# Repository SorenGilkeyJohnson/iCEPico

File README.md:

# iCEPico

> A compact development board combining the **RP2350** microcontroller and the **ICE40UP5K-SG48I** FPGA in a Raspberry Pi Pico form factor.

---

## Overview

The iCEPico is a custom PCB that pairs the RP2350 with the Lattice ICE40UP5K-SG48I FPGA. The board is modelled after the Raspberry Pi Pico, with the addition of the FPGA and a +1V2 regulator to supply it. The board matches the physical dimensions of the Pico, though it does **not** replicate the Pico's pinout.

I made this project because I wanted to learn FPGA design. Initially, I thought about using a BGA package but decided to go with QFN instead due to PCB costs and complexity. I had previously designed for the RP2040 but never the RP2350. I plan to use the project as a general-purpose dev board, a learning tool for FPGAs for me, and to teach students at my school's robotics club.

---
[Here is KiCanvas!](https://kicanvas.org/?repo=https%3A%2F%2Fgithub.com%2FSorenGilkeyJohnson%2FiCEPico%2Ftree%2Fmain%2FKiCad)

## Board Images

<table>
  <tr>
    <td align="center"><strong>Top View</strong></td>
    <td align="center"><strong>Bottom View</strong></td>
  </tr>
  <tr>
    <td></td>
    <td></td>
  </tr>
  <tr>
    <td align="center"><strong>3D Top</strong></td>
    <td align="center"><strong>3D Bottom</strong></td>
  </tr>
  <tr>
    <td></td>
    <td></td>
  </tr>
</table>

 [View Schematic (PDF)](Images/ICE40UP5K-SG48I_Schematic.pdf)

---

## Hardware

| Component | Part |
|-----------|------|
| Microcontroller | RP2350 |
| FPGA | Lattice ICE40UP5K-SG48I |
| QSPI Flash | W25Q128JVP |
| 3.3V Regulator | AP63203 (Buck) |
| 1.2V Regulator | TLV75612PDBV (LDO) |

### RP2350 <-> FPGA Interconnect

The FPGA flash is the RP2350 via bit-banging. The two chips share **8 GPIO lines** aligned to the RP2350's HSTX peripheral.

### PCB Stack-Up

| Layer | Function |
|-------|----------|
| 1 | Signal / Components |
| 2 | GND |
| 3 | PWR (primarily 3V3) |
| 4 | Signal |

---

## Power

The board can be powered via:
- **USB-C**      : 5V VBUS through a Schottky diode
- **VIN header** : direct voltage input

---

## Programming

| Method | Target | Description |
|--------|--------|-------------|
| USB (UF2) | RP2350 | Drag-and-drop bootloader over USB-C |
| SWD | RP2350 | Debug header for OpenOCD / probe-rs |
| Bit-bang (via RP2350) | ICE40 FPGA | FPGA bitstream loaded by the RP2350 firmware |

---

## Pinout

| Pin | Left Signal | | Right Signal | Pin |
|-----|------------|---|-------------|-----|
| 1  | GND        | | +3V3        | 2  |
| 3  | GPIO0      | | +VIN        | 4  |
| 5  | GPIO1      | | ADC2        | 6  |
| 7  | GPIO2      | | ADC1        | 8  |
| 9  | GPIO3      | | ADC0        | 10 |
| 11 | GPIO4      | | GPIO24      | 12 |
| 13 | GPIO5      | | GPIO23      | 14 |
| 15 | GPIO6      | | GPIO22      | 16 |
| 17 | IOT_37     | | IOB_16      | 18 |
| 19 | IOT_36     | | IOB_8       | 20 |
| 21 | IOT_39     | | IOB_9       | 22 |
| 23 | IOT_38     | | IOB_6       | 24 |
| 25 | IOT_41     | | IOB_4       | 26 |
| 27 | IOT_42     | | IOB_2       | 28 |
| 29 | IOT_43     | | IOB_0       | 30 |
| 31 | IOT_44     | | IOB_5       | 32 |
| 33 | IOT_48     | | IOB_3       | 34 |
| 35 | GND        | | GND         | 36 |
| 37 | IOT_45     | | IOT_49      | 38 |
| 39 | IOT_50     | | IOT_51      | 40 |

---

## Repository Structure

```
iCEPico/
├── Images/                          # Board renders and schematic export
│   ├── Bottom_View_PCB.png
│   ├── ICE40UP5K-SG48I_3D_Bottom.png
│   ├── ICE40UP5K-SG48I_3D_Top.png
│   ├── ICE40UP5K-SG48I_Schematic.pdf
│   └── Top_View_PNG.png
├── KiCad/                           # KiCad project files
│   ├── ICE40UP5K-SG48I.kicad_pcb
│   ├── ICE40UP5K-SG48I.kicad_prl
│   ├── ICE40UP5K-SG48I.kicad_pro
│   └── ICE40UP5K-SG48I.kicad_sch
├── fabrication/                     # Fabrication outputs
│   ├── bom.csv
│   ├── gerbers.zip
│   └── pick_and_place.csv
├── hardware/                        # Hardware source files
│   ├── ICE40UP5K-SG48I.kicad_pcb
│   ├── ICE40UP5K-SG48I.kicad_pro
│   └── ICE40UP5K-SG48I.kicad_sch
├── LICENSE
└── README.md
```

---

## License

See [LICENSE](LICENSE) for details.

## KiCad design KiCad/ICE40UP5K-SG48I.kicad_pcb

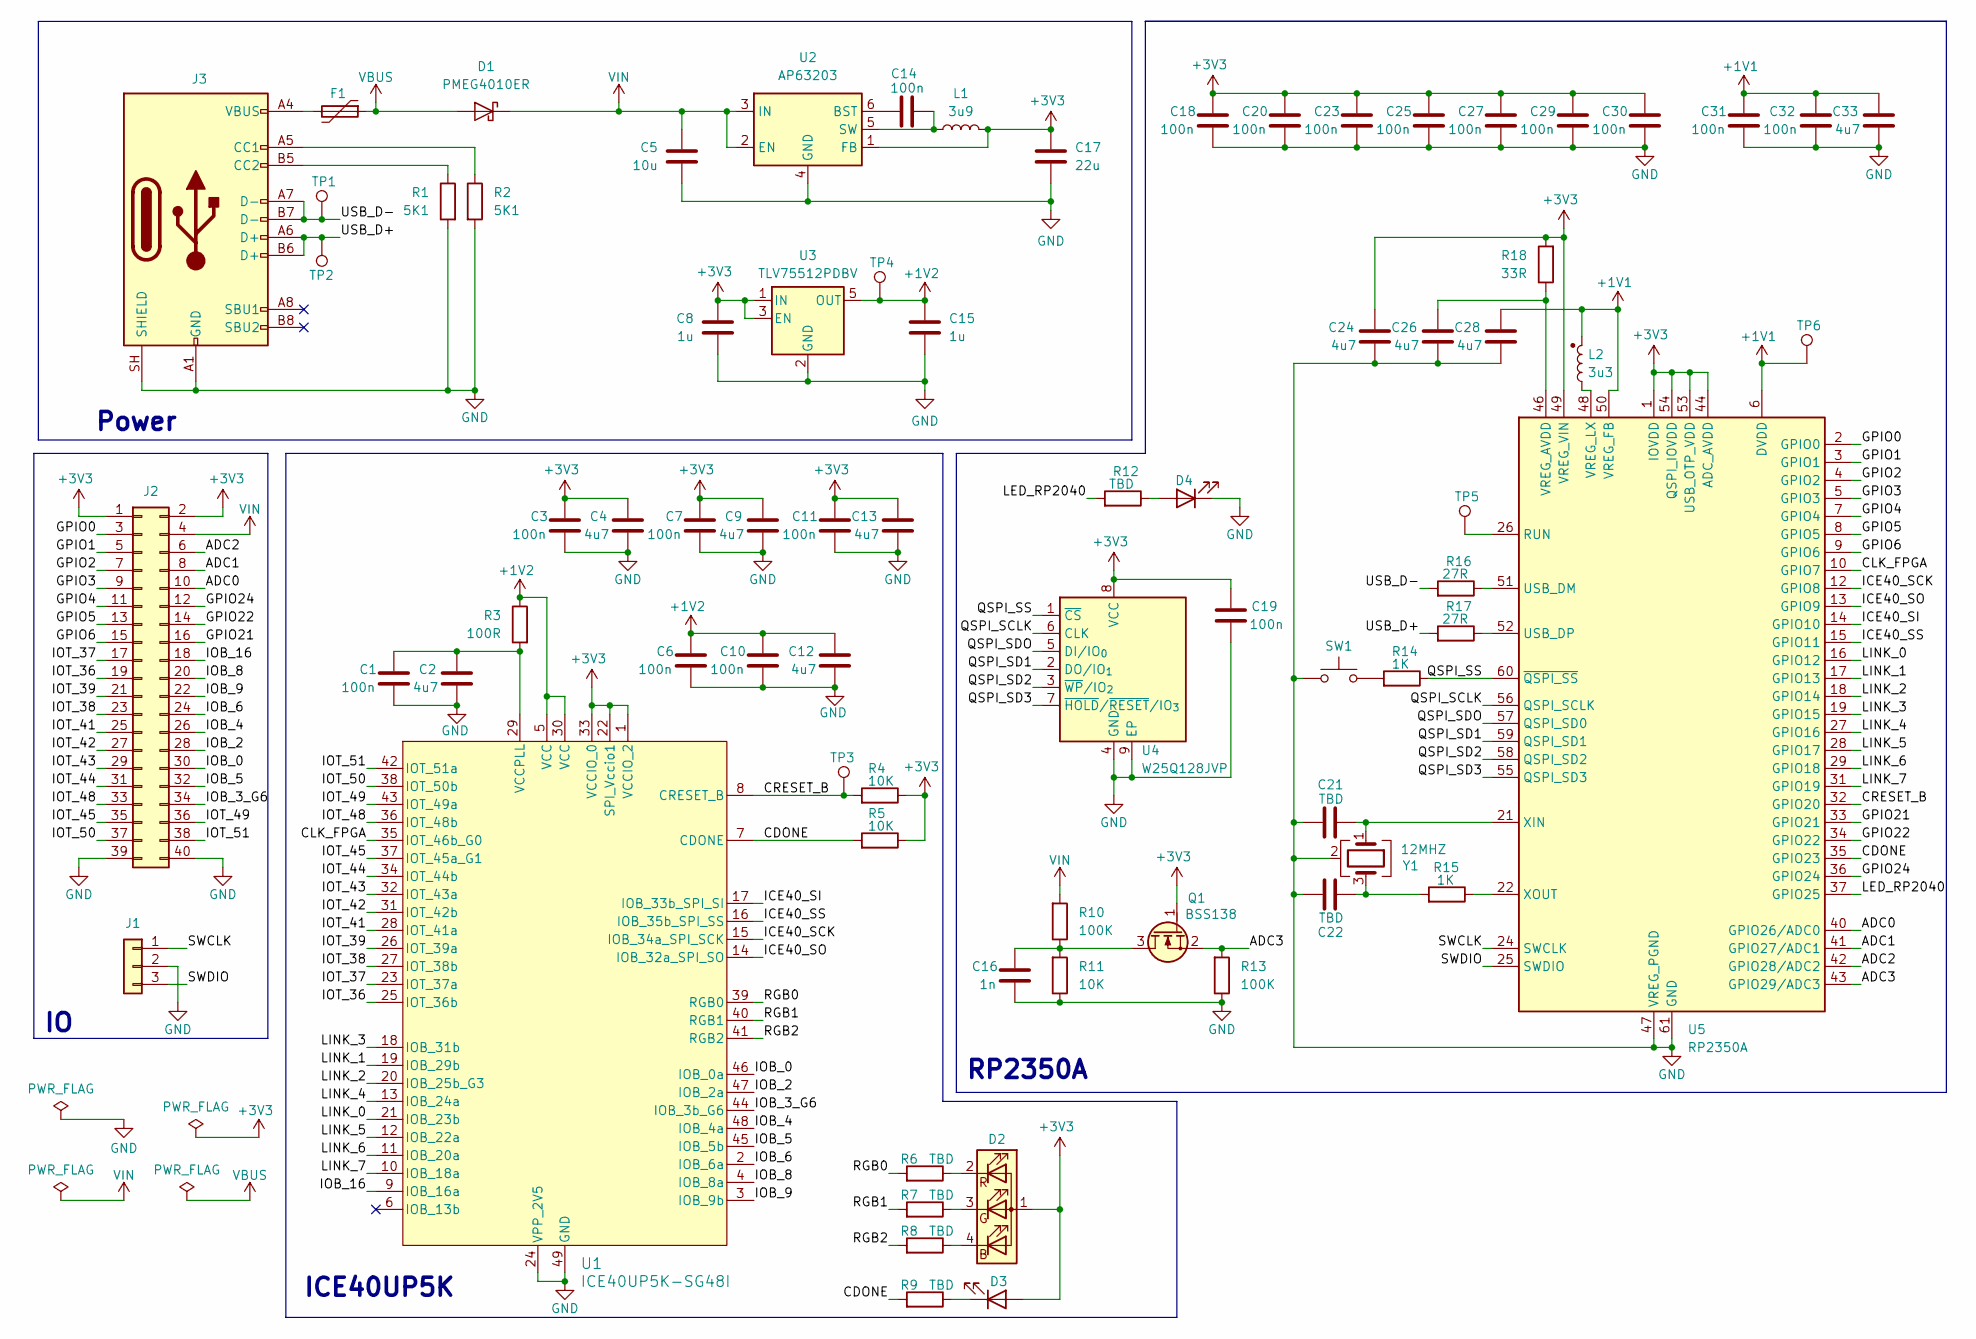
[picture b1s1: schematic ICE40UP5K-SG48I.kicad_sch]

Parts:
C1, C3, C6, C7, C10, C11, C14, C18, C19, C20, C23, C25, C27, C29, C30, C31, C32: 100n; C_0402_1005Metric
C2, C4, C9, C12, C13, C24, C26, C28, C33: 4u7; C_0402_1005Metric
C5: 10u; C_0805_2012Metric
C8, C15: 1u; C_0402_1005Metric
C16: 1n; C_0402_1005Metric
C17: 22u; C_0805_2012Metric
C21, C22: TBD; C_0402_1005Metric
D1: PMEG4010ER; Nexperia_CFP3_SOD-123W
D2: LED_ARGB; LED_SK6812_EC15_1.5x1.5mm
D3, D4: LED; LED_0402_1005Metric
F1: Polyfuse; Fuse_0603_1608Metric
J1: Conn_01x03; PinHeader_1x03_P2.54mm_Vertical
J2: Conn_02x20_Odd_Even; PinHeader_2x20_P2.54mm_Vertical
J3: USB_C_Receptacle_USB2.0_16P; USB_C_Receptacle_GCT_USB4105-xx-A_16P_TopMnt_Horizontal
L1: 3u9; L_Chilisin_BWVS00404012
L2: 3u3; L_Changjiang_FTC201607S
Q1: BSS138; SOT-23
R1, R2: 5K1; R_0402_1005Metric
R3: 100R; R_0402_1005Metric
R4, R5, R11: 10K; R_0402_1005Metric
R6, R7, R8, R9, R12: TBD; R_0402_1005Metric
R10, R13: 100K; R_0402_1005Metric
R14, R15: 1K; R_0402_1005Metric
R16, R17: 27R; R_0402_1005Metric
R18: 33R; R_0402_1005Metric
SW1: SW_MEC_5G; SW_3_42 4-PIN Button
TP1, TP2, TP3, TP4, TP5, TP6: TestPoint; TestPoint_Pad_D1.0mm
U1: ICE40UP5K-SG48I; QFN-48-1EP_7x7mm_P0.5mm_EP5.3x5.3mm
U2: AP63203; TSOT-23-6
U3: TLV75512PDBV; SOT-23-5
U4: W25Q128JVP; WSON-8-1EP_6x5mm_P1.27mm_EP3.4x4.3mm
U5: RP2350A; QFN-60-1EP_7x7mm_P0.4mm_EP3.4x3.4mm
Y1: 12MHZ; Crystal_SMD_3225-4Pin_3.2x2.5mm

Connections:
+1V1: C28.1, C31.1, C32.1, C33.1, L2.1, TP6.1 (1_1), U5.6 (DVDD), U5.23 (DVDD), U5.39 (DVDD), U5.50 (VREG_FB)
+1V2: C6.1, C10.1, C12.1, C15.1, R3.1, TP4.1 (1_1), U1.5 (VCC), U1.30 (VCC), U3.5 (OUT)
+3V3: C3.1, C4.1, C7.1, C8.1, C9.1, C11.1, C13.1, C17.1, C18.1, C19.1, C20.1, C23.1, C24.1, C25.1, C27.1, C29.1, C30.1, D2.1 (A), D3.2 (A), J2.1, J2.2, L1.2, Q1.1 (G), R4.1, R5.1, R18.1, U1.1 (VCCIO_2), U1.22 (SPI_Vccio1), U1.33 (VCCIO_0), U2.1 (FB), U3.1 (IN), U3.3 (EN), U4.8 (VCC), U5.1 (IOVDD), U5.11 (IOVDD), U5.20 (IOVDD), U5.30 (IOVDD), U5.38 (IOVDD), U5.44 (ADC_AVDD), U5.45 (IOVDD), U5.49 (VREG_VIN), U5.53 (USB_OTP_VDD), U5.54 (QSPI_IOVDD)
/ADC0: J2.10, U5.40 (GPIO26/ADC0)
/ADC1: J2.8, U5.41 (GPIO27/ADC1)
/ADC2: J2.6, U5.42 (GPIO28/ADC2)
/ADC3: Q1.2 (S), R13.1, U5.43 (GPIO29/ADC3)
/CDONE: R5.2, R9.2, U1.7 (CDONE), U5.35 (GPIO23)
/CLK_FPGA: U1.35 (IOT_46b_G0), U5.10 (GPIO7)
/CRESET_B: R4.2, TP3.1 (1_1), U1.8 (CRESET_B), U5.32 (GPIO20)
/GPIO0: J2.3, U5.2 (GPIO0)
/GPIO1: J2.5, U5.3 (GPIO1)
/GPIO2: J2.7, U5.4 (GPIO2)
/GPIO3: J2.9, U5.5 (GPIO3)
/GPIO4: J2.11, U5.7 (GPIO4)
/GPIO5: J2.13, U5.8 (GPIO5)
/GPIO6: J2.15, U5.9 (GPIO6)
/GPIO21: J2.16, U5.33 (GPIO21)
/GPIO22: J2.14, U5.34 (GPIO22)
/GPIO24: J2.12, U5.36 (GPIO24)
/ICE40_SCK: U1.15 (IOB_34a_SPI_SCK), U5.12 (GPIO8)
/ICE40_SI: U1.17 (IOB_33b_SPI_SI), U5.14 (GPIO10)
/ICE40_SO: U1.14 (IOB_32a_SPI_SO), U5.13 (GPIO9)
/ICE40_SS: U1.16 (IOB_35b_SPI_SS), U5.15 (GPIO11)
/IOB_0: J2.30, U1.46 (IOB_0a)
/IOB_2: J2.28, U1.47 (IOB_2a)
/IOB_3_G6: J2.34, U1.44 (IOB_3b_G6)
/IOB_4: J2.26, U1.48 (IOB_4a)
/IOB_5: J2.32, U1.45 (IOB_5b)
/IOB_6: J2.24, U1.2 (IOB_6a)
/IOB_8: J2.20, U1.4 (IOB_8a)
/IOB_9: J2.22, U1.3 (IOB_9b)
/IOB_16: J2.18, U1.9 (IOB_16a)
/IOT_36: J2.19, U1.25 (IOT_36b)
/IOT_37: J2.17, U1.23 (IOT_37a)
/IOT_38: J2.23, U1.27 (IOT_38b)
/IOT_39: J2.21, U1.26 (IOT_39a)
/IOT_41: J2.25, U1.28 (IOT_41a)
/IOT_42: J2.27, U1.31 (IOT_42b)
/IOT_43: J2.29, U1.32 (IOT_43a)
/IOT_44: J2.31, U1.34 (IOT_44b)
/IOT_45: J2.35, U1.37 (IOT_45a_G1)
/IOT_48: J2.33, U1.36 (IOT_48b)
/IOT_49: J2.36, U1.43 (IOT_49a)
/IOT_50: J2.37, U1.38 (IOT_50b)
/IOT_51: J2.38, U1.42 (IOT_51a)
/LED_RP2040: R12.2, U5.37 (GPIO25)
/LINK_0: U1.21 (IOB_23b), U5.16 (GPIO12)
/LINK_1: U1.19 (IOB_29b), U5.17 (GPIO13)
/LINK_2: U1.20 (IOB_25b_G3), U5.18 (GPIO14)
/LINK_3: U1.18 (IOB_31b), U5.19 (GPIO15)
/LINK_4: U1.13 (IOB_24a), U5.27 (GPIO16)
/LINK_5: U1.12 (IOB_22a), U5.28 (GPIO17)
/LINK_6: U1.11 (IOB_20a), U5.29 (GPIO18)
/LINK_7: U1.10 (IOB_18a), U5.31 (GPIO19)
/QSPI_SCLK: U4.6 (CLK), U5.56 (QSPI_SCLK)
/QSPI_SD1: U4.2 (DO/IO_{1}), U5.59 (QSPI_SD1)
/QSPI_SD2: U4.3 (~WP/IO_{2}), U5.58 (QSPI_SD2)
/QSPI_SD3: U4.7 (~HOLD/~RESET/IO_{3}), U5.55 (QSPI_SD3)
/QSPI_SDO: U4.5 (DI/IO_{0}), U5.57 (QSPI_SD0)
/QSPI_SS: R14.1, U4.1 (~CS), U5.60 (~QSPI_SS)
/RGB0: R6.2, U1.39 (RGB0)
/RGB1: R7.2, U1.40 (RGB1)
/RGB2: R8.2, U1.41 (RGB2)
/SWCLK: J1.1, U5.24 (SWCLK)
/SWDIO: J1.3, U5.25 (SWDIO)
/USB_D+: J3.A6 (D+), J3.B6 (D+), R17.2, TP2.1 (1_1)
/USB_D-: J3.A7 (D-), J3.B7 (D-), R16.2, TP1.1 (1_1)
GND: C1.2, C2.2, C3.2, C4.2, C5.2, C6.2, C7.2, C8.2, C9.2, C10.2, C11.2, C12.2, C13.2, C15.2, C16.2, C17.2, C18.2, C19.2, C20.2, C21.1, C22.1, C23.2, C24.2, C25.2, C26.2, C27.2, C28.2, C29.2, C30.2, C31.2, C32.2, C33.2, D4.1 (K), J1.2, J2.39, J2.40, J3.A1 (GND), J3.A12 (GND), J3.B1 (GND), J3.B12 (GND), J3.SH (SHIELD), R1.2, R2.2, R11.2, R13.2, SW1.3, SW1.4 (B), U1.24 (VPP_2V5), U1.49 (GND), U2.4 (GND), U3.2 (GND), U3.4 (NC), U4.4 (GND), U4.9 (EP), U5.47 (VREG_PGND), U5.61 (GND), Y1.2 (G), Y1.4 (G)
unnamed: C22.2, R15.2, Y1.3
unnamed: D2.4 (BK), R8.1
unnamed: D2.3 (GK), R7.1
unnamed: D2.2 (RK), R6.1
unnamed: D3.1 (K), R9.1
unnamed: D4.2 (A), R12.1
unnamed: F1.2, J3.A4 (VBUS), J3.A9 (VBUS), J3.B4 (VBUS), J3.B9 (VBUS)
unnamed: J3.A5 (CC1), R2.1
unnamed: J3.B5 (CC2), R1.1
unnamed: C16.1, Q1.3 (D), R10.2, R11.1
unnamed: R14.2, SW1.1, SW1.2 (A)
unnamed: C1.1, C2.1, R3.2, U1.29 (VCCPLL)
unnamed: C14.1, U2.6 (BST)
unnamed: C14.2, L1.1, U2.5 (SW)
unnamed: TP5.1 (1_1), U5.26 (RUN)
unnamed: R16.1, U5.51 (USB_DM)
unnamed: R17.1, U5.52 (USB_DP)
unnamed: C26.1, R18.2, U5.46 (VREG_AVDD)
unnamed: L2.2, U5.48 (VREG_LX)
unnamed: C21.2, U5.21 (XIN), Y1.1
unnamed: R15.1, U5.22 (XOUT)
VBUS: D1.2 (A), F1.1
VIN: C5.1, D1.1 (K), J2.4, R10.1, U2.2 (EN), U2.3 (IN)

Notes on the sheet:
Power
RP2350A
ICE40UP5K

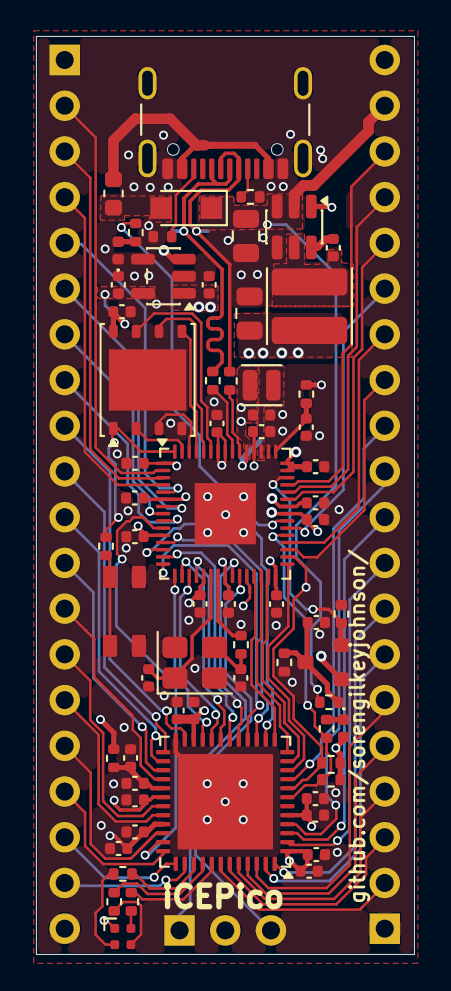
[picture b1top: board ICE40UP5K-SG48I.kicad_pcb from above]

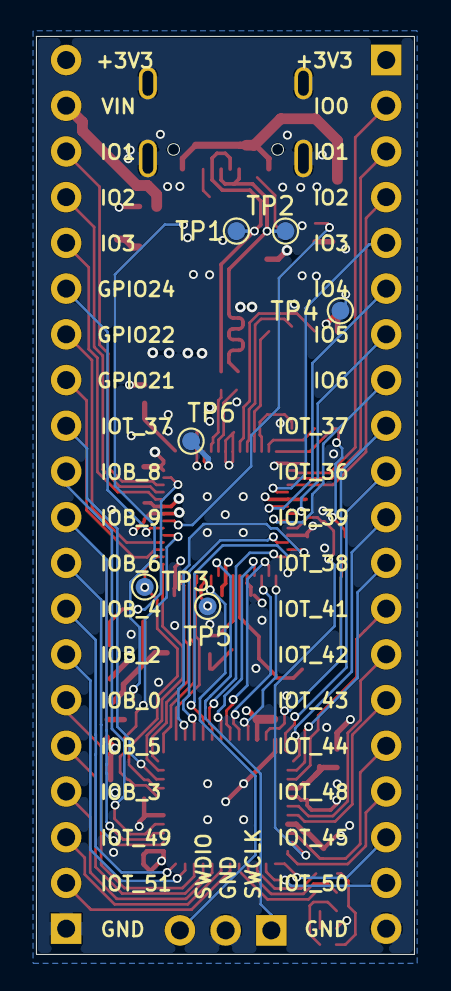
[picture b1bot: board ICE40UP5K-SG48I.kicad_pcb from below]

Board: 4 copper layers, 21.0 x 51.0 mm, 75 parts (6 on the bottom side), 92 nets.

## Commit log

2026-05-27 Hardware
2026-05-29 Rename Screenshot 2026-05-25 161220.png to topview_pcb.png
2026-05-29 Rename Screenshot 2026-05-25 164551.png to bottomview_pcb.png
2026-05-29 Rename ICE40UP5K-SG48I.png to ICE40UP5K-SG48I_3D_Top.png
2026-05-29 Rename ICE40UP5K-SG48I.pdf to ICE40UP5K-SG48I_Schematic.pdf
2026-05-29 Rename topview_pcb.png to photos/Top_View_PNG.png
2026-05-29 Rename bottomview_pcb.png to photos/Bottom_View_PCB.png
2026-05-29 Rename Bottom_View_PCB.png to Bottom_View_PCB.png
2026-05-29 Rename Top_View_PNG.png to Top_View_PNG.png
2026-05-29 Rename ICE40UP5K-SG48I_3D_Top.png to Images/ICE40UP5K-SG48I_3D_Top.png
2026-05-29 Rename ICE40UP5K-SG48I_Schematic.pdf to Images/ICE40UP5K-SG48I_Schematic.pdf
2026-05-29 Rename ICE40UP5K-SG48I.png to ICE40UP5K-SG48I_3D_Bottom.png
2026-05-29 Rename ICE40UP5K-SG48I_21.0x51.0mm_for_Default.zip to fabrication/gerber.zip
2026-05-29 Rename gerber.zip to gerbers.zip
2026-05-29 Add bom.csv to the project
2026-05-29 Rename bom.csv to fabrication/bom.csv
2026-05-29 Add CERN Open Hardware Licence Version 2
    Added CERN Open Hardware Licence Version 2 - Strongly Reciprocal to the project.
2026-05-29 Add pick_and_place.csv to fabrication directory
2026-05-29 Rename ICE40UP5K-SG48I.kicad_prl to fabrication/ICE40UP5K-SG48I.kicad_prl
2026-05-29 Add KiCad project file for ICE40UP5K-SG48I
2026-05-29 Rename ICE40UP5K-SG48I.kicad_pcb to KiCad/ICE40UP5K-SG48I.kicad_pcb
2026-05-29 Rename ICE40UP5K-SG48I.kicad_pro to KiCad/ICE40UP5K-SG48I.kicad_pro
2026-05-29 Rename ICE40UP5K-SG48I.kicad_sch to KiCad/ICE40UP5K-SG48I.kicad_sch
2026-05-29 Enhance README with detailed board information
    Expanded the README to provide detailed information about the iCEPico development board, including hardware specifications, power options, programming methods, pinout, and repository structure.
2026-05-30 Rename ICE40UP5K-SG48I.pdf to Images/ICE40UP5K-SG48I_Schematic.pdf
2026-06-06 added kicanvas
